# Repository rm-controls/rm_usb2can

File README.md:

# rm_usb2can

&nbsp;&nbsp;&nbsp;&nbsp;

English/[中文](https://github.com/rm-controls/rm_usb2can/blob/main/README_CN.md)

***

### Brief Introduction

&nbsp;&nbsp;&nbsp;&nbsp;The purpose of this project is to provide [Intel® NUC](https://www.intel.com/content/www/us/en/products/details/nuc.html) and other x86 device with a CAN (Controller Area Network) peripheral interface. Since NUC and most x86 device does not have simple peripheral interfaces such as SPI (Serial Peripheral Interface), it is impossible to use SPI to can chips such as MCP2515. Therefore, the project is developed based on the open source solution [candleLight](https://github.com/candle-usb/candleLight_fw/tree/master) on GitHub, and STM32F072CBT6 is used as the main control chip to realize the function of USB (Universal Serial Bus) to can. STM32F072CBT6 has USB full speed peripherals and can peripherals that can work at the same time. It is packaged as QFP48 (Quad Flat Package) and is an excellent solution.The following figure shows the physical connection between Intel NUC and usb2can.

***

### Develop Tools

+ EDA Tool: KiCAD 6.0.9
+ Compiler: gcc-arm-none-eabi 10.3.1 20210824 (release)
+ Programming Tool: STM32CubeProgrammer v2.13.0

***

### Directory Structure

+ manufacture: USB2CAN production manufacturing file.
+ program: Github open source program [candleLight](https://github.com/candle-usb/candleLight_fw/tree/master) modified source code.
+ circuit: Circuit schematic and PCB source files designed with KiCAD.
+ image: Images of README.

***

### Circuit Design

#### Key Points Of Schematic Design

&nbsp;&nbsp;&nbsp;&nbsp;USB HUB Circuit Design: since the whole vehicle needs at least two can buses to ensure the integrity of the data packet returned by the motor, we use SL2.1s as the USB HUB chip to realize the scheme of USB one driving four. In addition, we also use Schmidt trigger to realize the power on sequence to ensure that the enumeration sequence of USB devices is consistent after each power on.

&nbsp;&nbsp;&nbsp;&nbsp;USB To CAN Circuit Design: use STM32F072CBT6 to realize the function of USB to can. The CAN level conversion chip uses the TJA1050 chip, which uses a 5V power supply and greatly reduces the probability of CAN transceiver damage due to the chip's higher common mode withstand voltage. The purpose of R6 and R7 resistors in the figure is to change the boot mode of STM32, so that STM32 can switch between DFU (Device Firmware Upgrade) burning mode and flash mode by changing the short circuit mode of R6 and R7, so as to facilitate firmware burning.

#### Key Points Of PCB Layout And Wiring

1. All USB buses need to be set as differential pairs, and the wiring rules of differential signals shall be strictly followed during wiring.
2. All CAN buses need to be set as differential pairs, and the wiring rules of differential signals shall be strictly followed during wiring.
3. The bottom of crystal oscillator and resonant capacitor should be hollowed out without copper.
4. The power line width shall be greater than 0.3mm as far as possible to ensure that the power track does not collapse.

***

### Circuit Making

&nbsp;&nbsp;&nbsp;&nbsp;We provide Gerber files that can be used directly for manufacturing in the [manufacturer folder](https://github.com/rm-controls/rm_usb2can/tree/main/manufacture). This version can realize one way USB to 2 way CAN + 2 way UART, and its circuit schematic is shown in the [circuit folder](https://github.com/rm-controls/rm_usb2can/tree/main/circuit). You can submit the packaged Gerber file directly to a manufacturer (e.g., [PCB Way](https://www.pcbway.com/)) for production.

&nbsp;&nbsp;&nbsp;&nbsp;You can also find the corresponding BOM (Bill Of Material) table for the board in the [manufacturer folder](https://github.com/rm-controls/rm_usb2can/tree/main/manufacture) and solder the components to the already made PCB according to this table. After the soldering is complete, please carefully check whether there is residual solder between the pins, that will lead to a short circuit on the board, and you also have to check whether the pins have the phenomenon of false solder.

&nbsp;&nbsp;&nbsp;&nbsp;After welding, use a multimeter to check whether there is a short circuit between 5V power interface and GND, and whether there is a short circuit between 3.3V power output and GND. When the above situation does not occur, connect the board to the USB port of the computer. At this time, you should see that the power indicator on the board is on, and the computer can recognize the USB HUB chip.

**Note: do not weld the up / down resistance used to switch STM32 download mode at the same time, as it may cause a short circuit between the power supply and GND!**

***

### Firmware Programming

&nbsp;&nbsp;&nbsp;&nbsp;You can download the compiled firmware in [Release](https://github.com/rm-controls/rm_usb2can/releases) page, or follow the [candlelight documentation](https://github.com/candle-usb/candleLight_fw/tree/master#building) to compile firmware by yourself. Finally, you will get the .bin file. We use [STM32CubeProgrammer](https://www.st.com/en/development-tools/stm32cubeprog.html) to burn the firmware into STM32 through USB. The steps to download firmware are shown below:

1. Remove the pull-down resistance of BOOT0 pin of STM32 and weld the pull-up resistance.
2. Connect the board to the USB port of the computer and open STM32CubeProgrammer.
3. Click the three buttons shown in the following figure in STM32CubeProgrammer to search for available STM32 devices.

4. After successful connection, click the "Read" button to read the firmware and select the prepared firmware.

5. Click "Download" to download the firmware. After the download is successful, you can see the successful information.

6. Remove the pull-up resistance of BOOT0 pin on STM32 and weld the pull-down resistance. Power on again at this time, and the firmware will start running on STM32.

***

### Test Features On Ubuntu

1. Install dependent packages:

```bash
$ sudo apt-get update && sudo apt-get -y upgrade
$ sudo apt-get install -y can-utils net-tools
```

2. Check whether can device is detected:

```bash
$ ifconfig -a
# If a device with can name is found in the list, it means that the device can be recognized
```

3. Connect the two can ports with a **straight line** to facilitate loop back test.
4. Initialize CAN0 and CAN1 devices with a bit rate of 1Mbits:

```bash
$ sudo ip link set can0 up type can bitrate 1000000
$ sudo ip link set can1 up type can bitrate 1000000
```

5. Open a new terminal to monitor the information received by can0:

```bash
$ candump can0
```

6. Sending information using can1 in a terminal:

```bash
$ cansend can1 200#5A5A5A5A5A5A5A5A
```

If you can see the following information from can1 in the terminal monitoring can0, it indicates that the communication is successful and the module works normally.

```bash
can0 200 [8] 5A 5A 5A 5A 5A 5A 5A 5A
```

***

### License

The source code is released under a [MIT License](https://github.com/rm-controls/rm_usb2can/blob/main/LICENSE).

**Affiliation：DynamicX<br>
Maintainer：YanzhenZhu, 2208213223@qq.com**

The product has been tested under Ubuntu 18.04, 20.04 and 22.04. This is research code, expect that it changes often and any fitness for a particular purpose is disclaimed.

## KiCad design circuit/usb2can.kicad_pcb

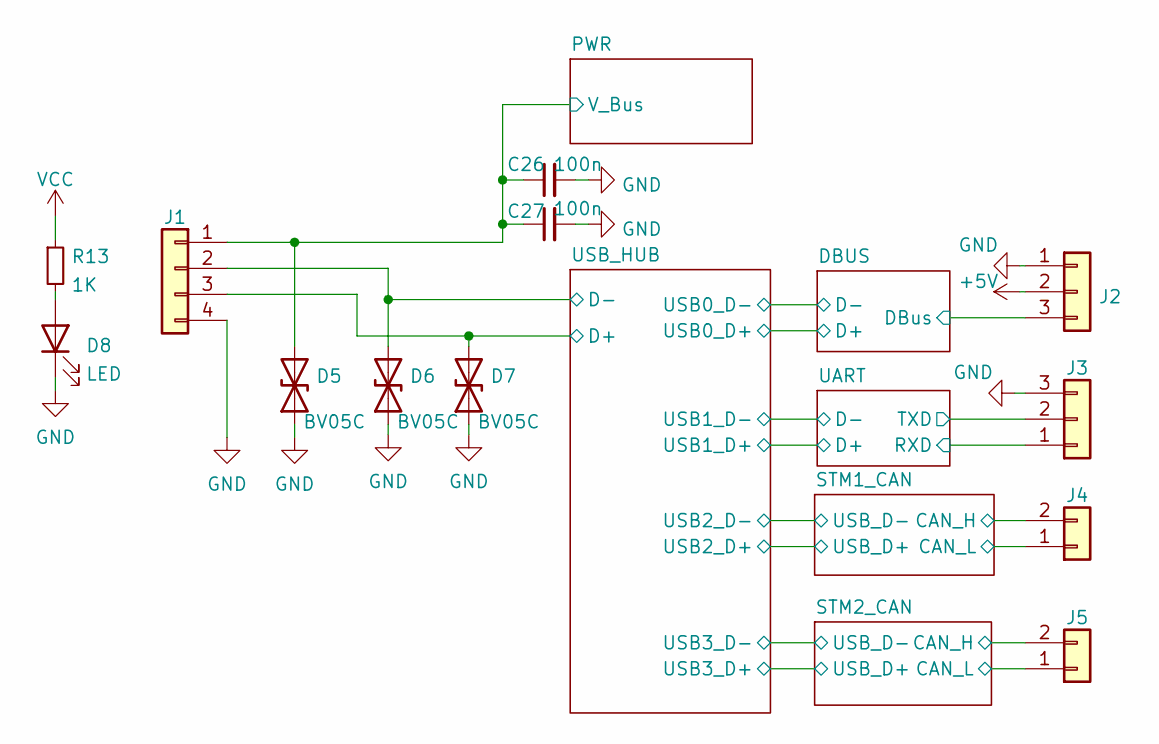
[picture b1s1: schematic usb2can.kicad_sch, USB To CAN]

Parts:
C26, C27: 100n; C_0603_1608Metric
D5, D6, D7: BV05C; D_SOD-323
D8: LED; LED_0603_1608Metric
J1: Conn_01x04; Molex_CLIK-Mate_502386-0470_1x04-1MP_P1.25mm_Horizontal
J2, J3: Conn_01x03; JST_GH_SM03B-GHS-TB_1x03-1MP_P1.25mm_Horizontal
J4, J5: Conn_01x02; JST_GH_SM02B-GHS-TB_1x02-1MP_P1.25mm_Horizontal
R13: 1K; R_0603_1608Metric

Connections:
+5V: C26.1, C27.1, D5.2 (A2), J1.1, J2.2; also elsewhere on the board
/DBUS/DBus: J2.3; also elsewhere on the board
/STM1_CAN/CAN_H: J4.2; also elsewhere on the board
/STM1_CAN/CAN_L: J4.1; also elsewhere on the board
/STM2_CAN/CAN_H: J5.2; also elsewhere on the board
/STM2_CAN/CAN_L: J5.1; also elsewhere on the board
/UART/RXD: J3.1; also elsewhere on the board
/UART/TXD: J3.2; also elsewhere on the board
/USB_HUB/D+: D7.2 (A2), J1.3; also elsewhere on the board
/USB_HUB/D-: D6.2 (A2), J1.2; also elsewhere on the board
GND: C26.2, C27.2, D5.1 (A1), D6.1 (A1), D7.1 (A1), D8.1 (K), J1.4, J2.1, J3.3; also elsewhere on the board
unnamed: D8.2 (A), R13.2
VCC: R13.1; also elsewhere on the board

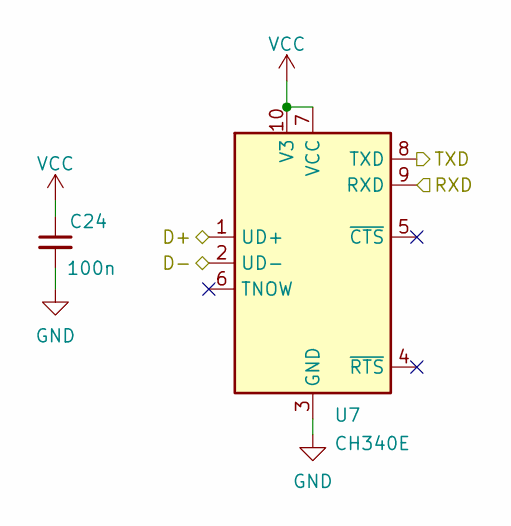
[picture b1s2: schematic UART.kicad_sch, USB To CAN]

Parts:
C24: 100n; C_0603_1608Metric
U7: CH340E; MSOP-10_3x3mm_P0.5mm

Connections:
/UART/D+: U7.1 (UD+); also elsewhere on the board
/UART/D-: U7.2 (UD-); also elsewhere on the board
/UART/RXD: U7.9 (RXD); also elsewhere on the board
/UART/TXD: U7.8 (TXD); also elsewhere on the board
GND: C24.2, U7.3 (GND); also elsewhere on the board
VCC: C24.1, U7.7 (VCC), U7.10 (V3); also elsewhere on the board

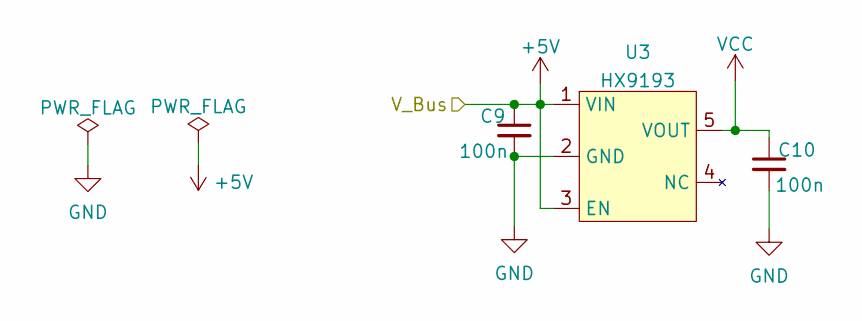
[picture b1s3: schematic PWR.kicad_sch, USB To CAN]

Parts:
C9, C10: 100n; C_0603_1608Metric
U3: HX9193; SOT-23-5_HandSoldering

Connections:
+5V: C9.1, U3.1 (VIN), U3.3 (EN); also elsewhere on the board
GND: C9.2, C10.2, U3.2 (GND); also elsewhere on the board
VCC: C10.1, U3.5 (VOUT); also elsewhere on the board

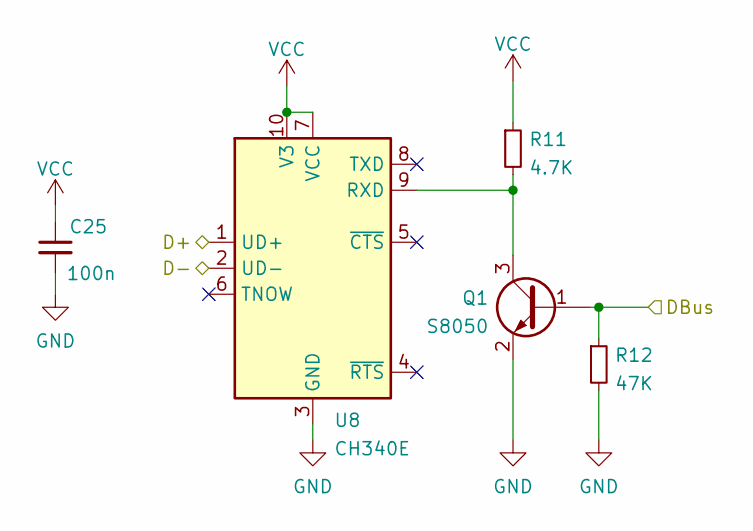
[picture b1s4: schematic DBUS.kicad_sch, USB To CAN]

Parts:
C25: 100n; C_0603_1608Metric
Q1: S8050; SOT-23
R11: 4.7K; R_0603_1608Metric
R12: 47K; R_0603_1608Metric
U8: CH340E; MSOP-10_3x3mm_P0.5mm

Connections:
/DBUS/D+: U8.1 (UD+); also elsewhere on the board
/DBUS/D-: U8.2 (UD-); also elsewhere on the board
/DBUS/DBus: Q1.1 (B), R12.1; also elsewhere on the board
GND: C25.2, Q1.2 (E), R12.2, U8.3 (GND); also elsewhere on the board
unnamed: Q1.3 (C), R11.2, U8.9 (RXD)
VCC: C25.1, R11.1, U8.7 (VCC), U8.10 (V3); also elsewhere on the board

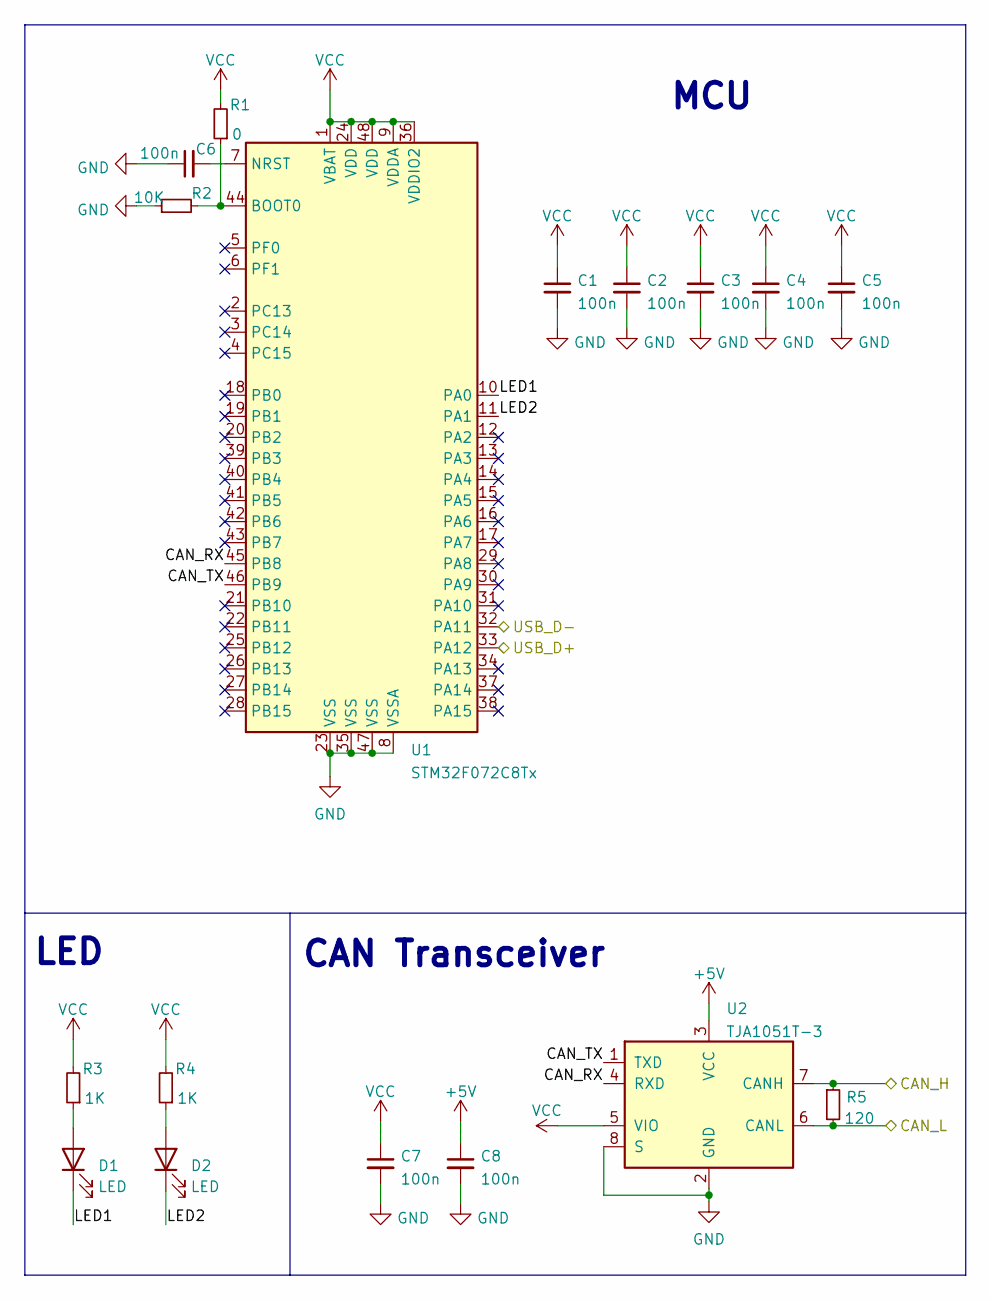
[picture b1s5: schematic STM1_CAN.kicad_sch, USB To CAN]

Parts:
C1, C2, C3, C4, C5, C6, C7, C8: 100n; C_0603_1608Metric
D1, D2: LED; LED_0603_1608Metric
R1: 0; R_0603_1608Metric
R2: 10K; R_0603_1608Metric
R3, R4: 1K; R_0603_1608Metric
R5: 120; R_0603_1608Metric
U1: STM32F072C8Tx; LQFP-48_7x7mm_P0.5mm
U2: TJA1051T-3; SOIC-8_3.9x4.9mm_P1.27mm

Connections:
+5V: C8.1, U2.3 (VCC); also elsewhere on the board
/STM1_CAN/CAN_H: R5.1, U2.7 (CANH); also elsewhere on the board
/STM1_CAN/CAN_L: R5.2, U2.6 (CANL); also elsewhere on the board
/STM1_CAN/CAN_RX: U1.45 (PB8), U2.4 (RXD)
/STM1_CAN/CAN_TX: U1.46 (PB9), U2.1 (TXD)
/STM1_CAN/LED1: D1.1 (K), U1.10 (PA0)
/STM1_CAN/LED2: D2.1 (K), U1.11 (PA1)
/STM1_CAN/USB_D+: U1.33 (PA12); also elsewhere on the board
/STM1_CAN/USB_D-: U1.32 (PA11); also elsewhere on the board
GND: C1.2, C2.2, C3.2, C4.2, C5.2, C6.1, C7.2, C8.2, R2.1, U1.8 (VSSA), U1.23 (VSS), U1.35 (VSS), U1.47 (VSS), U2.2 (GND), U2.8 (S); also elsewhere on the board
unnamed: C6.2, U1.7 (NRST)
unnamed: D1.2 (A), R3.1
unnamed: D2.2 (A), R4.1
unnamed: R1.1, R2.2, U1.44 (BOOT0)
VCC: C1.1, C2.1, C3.1, C4.1, C5.1, C7.1, R1.2, R3.2, R4.2, U1.1 (VBAT), U1.9 (VDDA), U1.24 (VDD), U1.36 (VDDIO2), U1.48 (VDD), U2.5 (VIO); also elsewhere on the board

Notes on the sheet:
CAN Transceiver
LED
MCU

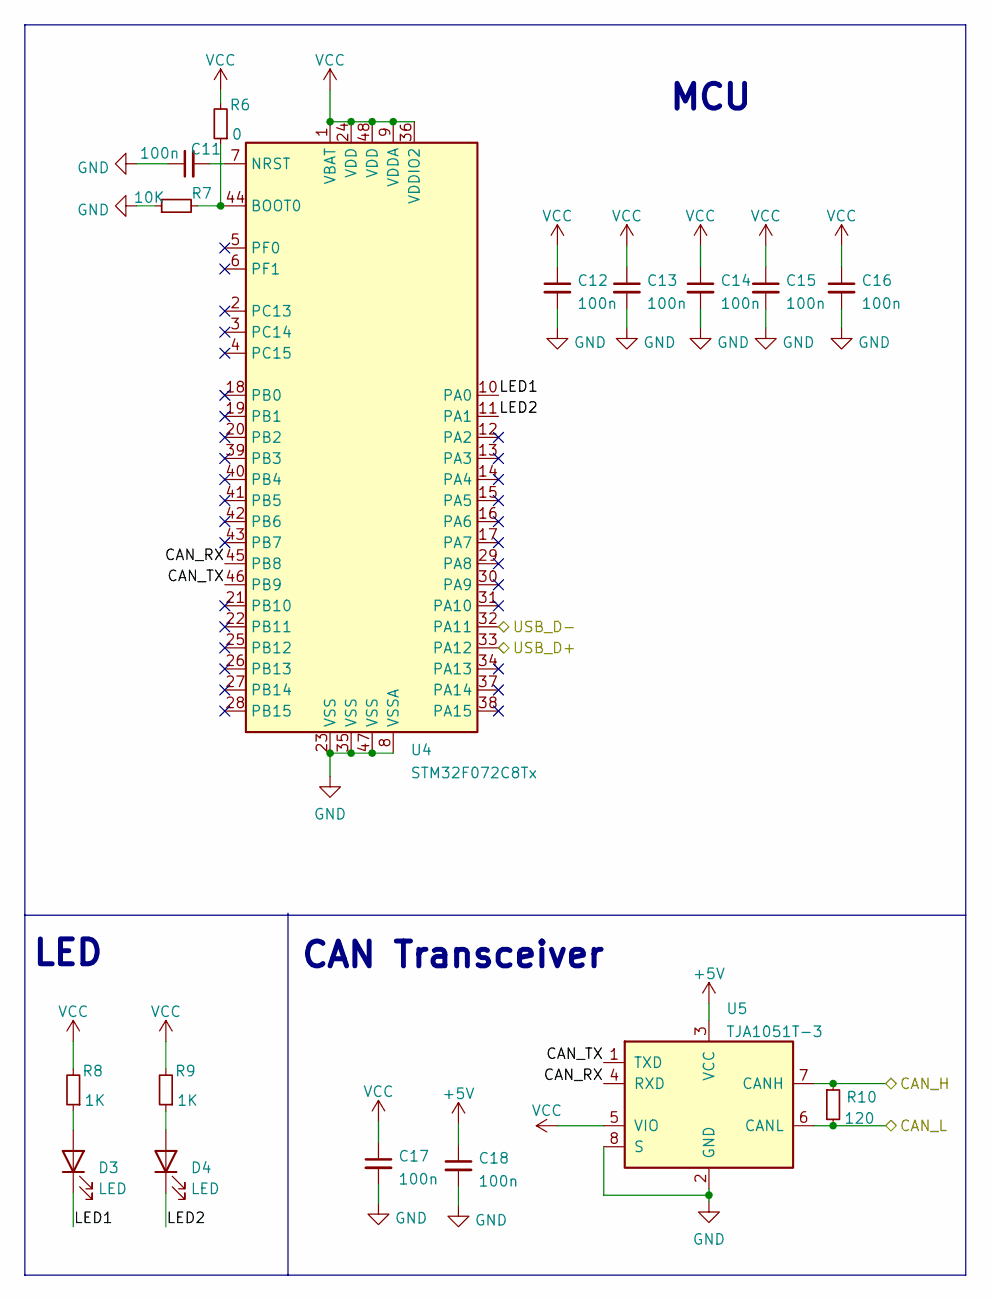
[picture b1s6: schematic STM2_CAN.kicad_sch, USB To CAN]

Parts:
C11, C12, C13, C14, C15, C16, C17, C18: 100n; C_0603_1608Metric
D3, D4: LED; LED_0603_1608Metric
R6: 0; R_0603_1608Metric
R7: 10K; R_0603_1608Metric
R8, R9: 1K; R_0603_1608Metric
R10: 120; R_0603_1608Metric
U4: STM32F072C8Tx; LQFP-48_7x7mm_P0.5mm
U5: TJA1051T-3; SOIC-8_3.9x4.9mm_P1.27mm

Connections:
+5V: C18.1, U5.3 (VCC); also elsewhere on the board
/STM2_CAN/CAN_H: R10.1, U5.7 (CANH); also elsewhere on the board
/STM2_CAN/CAN_L: R10.2, U5.6 (CANL); also elsewhere on the board
/STM2_CAN/CAN_RX: U4.45 (PB8), U5.4 (RXD)
/STM2_CAN/CAN_TX: U4.46 (PB9), U5.1 (TXD)
/STM2_CAN/LED1: D3.1 (K), U4.10 (PA0)
/STM2_CAN/LED2: D4.1 (K), U4.11 (PA1)
/STM2_CAN/USB_D+: U4.33 (PA12); also elsewhere on the board
/STM2_CAN/USB_D-: U4.32 (PA11); also elsewhere on the board
GND: C11.1, C12.2, C13.2, C14.2, C15.2, C16.2, C17.2, C18.2, R7.1, U4.8 (VSSA), U4.23 (VSS), U4.35 (VSS), U4.47 (VSS), U5.2 (GND), U5.8 (S); also elsewhere on the board
unnamed: C11.2, U4.7 (NRST)
unnamed: D3.2 (A), R8.1
unnamed: D4.2 (A), R9.1
unnamed: R6.1, R7.2, U4.44 (BOOT0)
VCC: C12.1, C13.1, C14.1, C15.1, C16.1, C17.1, R6.2, R8.2, R9.2, U4.1 (VBAT), U4.9 (VDDA), U4.24 (VDD), U4.36 (VDDIO2), U4.48 (VDD), U5.5 (VIO); also elsewhere on the board

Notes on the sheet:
LED
MCU
CAN Transceiver

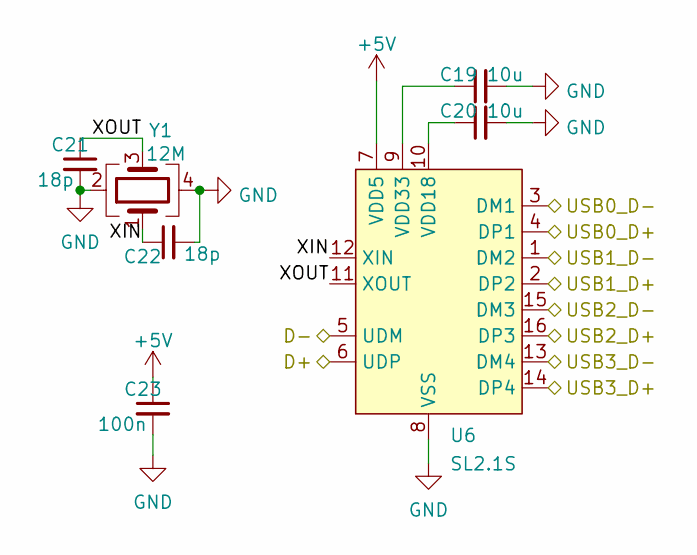
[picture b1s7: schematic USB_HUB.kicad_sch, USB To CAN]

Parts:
C19, C20: 10u; C_0603_1608Metric
C21, C22: 18p; C_0603_1608Metric
C23: 100n; C_0603_1608Metric
U6: SL2.1S; SL2.1S-SSOP-16
Y1: 12M; Crystal_SMD_3225-4Pin_3.2x2.5mm

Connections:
+5V: C23.1, U6.7 (VDD5); also elsewhere on the board
/DBUS/D+: U6.4 (DP1); also elsewhere on the board
/DBUS/D-: U6.3 (DM1); also elsewhere on the board
/STM1_CAN/USB_D+: U6.16 (DP3); also elsewhere on the board
/STM1_CAN/USB_D-: U6.15 (DM3); also elsewhere on the board
/STM2_CAN/USB_D+: U6.14 (DP4); also elsewhere on the board
/STM2_CAN/USB_D-: U6.13 (DM4); also elsewhere on the board
/UART/D+: U6.2 (DP2); also elsewhere on the board
/UART/D-: U6.1 (DM2); also elsewhere on the board
/USB_HUB/D+: U6.6 (UDP); also elsewhere on the board
/USB_HUB/D-: U6.5 (UDM); also elsewhere on the board
/USB_HUB/XIN: C22.1, U6.12 (XIN), Y1.1
/USB_HUB/XOUT: C21.1, U6.11 (XOUT), Y1.3
GND: C19.2, C20.2, C21.2, C22.2, C23.2, U6.8 (VSS), Y1.2, Y1.4; also elsewhere on the board
unnamed: C19.1, U6.9 (VDD33)
unnamed: C20.1, U6.10 (VDD18)

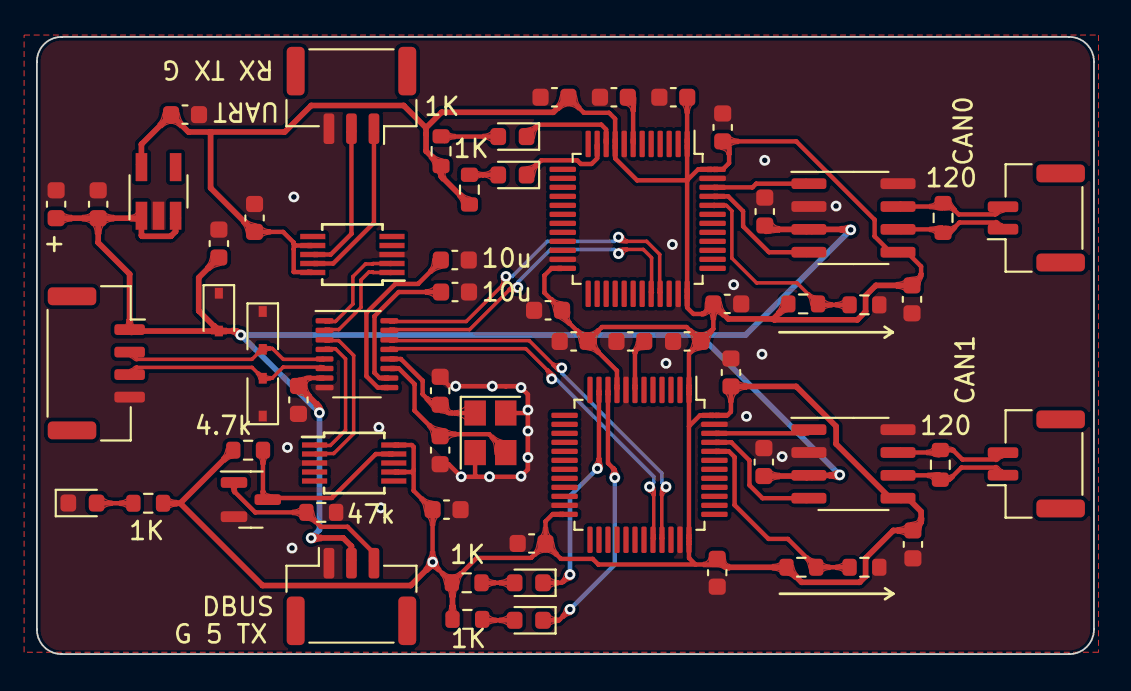
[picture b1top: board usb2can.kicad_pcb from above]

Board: 2 copper layers, 58.7 x 34.3 mm, 63 parts (0 on the bottom side), 42 nets.

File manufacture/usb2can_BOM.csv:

"ID";"指示符";"软件包";"数量";"名称";"供应商和参考";
1;"D3,D2,D1,D4,D8";"LED_0603_1608Metric";5;"LED";;;
2;"C9,C6,C26,C25,C5,C27,C16,C10,C7,C23,C17,C24,C12,C18,C2,C14,C3,C11,C13,C8,C1,C15,C4";"C_0603_1608Metric";23;"100n";;;
3;"R8,R4,R9,R3,R13";"R_0603_1608Metric";5;"1K";;;
4;"U5,U2";"SOIC-8_3.9x4.9mm_P1.27mm";2;"TJA1051T-3";;;
5;"U4,U1";"LQFP-48_7x7mm_P0.5mm";2;"STM32F072C8Tx";;;
6;"U6";"SL2.1S-SSOP-16";1;"SL2.1S";;;
7;"J1";"Molex_CLIK-Mate_502386-0470_1x04-1MP_P1.25mm_Horizontal";1;"Conn_01x04";;;
8;"C21,C22";"C_0603_1608Metric";2;"18p";;;
9;"Q1";"SOT-23";1;"S8050";;;
10;"J4,J5";"JST_GH_SM02B-GHS-TB_1x02-1MP_P1.25mm_Horizontal";2;"Conn_01x02";;;
11;"U3";"SOT-23-5_HandSoldering";1;"HX9193";;;
12;"D7,D5,D6";"D_SOD-323";3;"BV05C";;;
13;"R6,R1";"R_0603_1608Metric";2;"0";;;
14;"R11";"R_0603_1608Metric";1;"4.7K";;;
15;"R5,R10";"R_0603_1608Metric";2;"120";;;
16;"R2,R7";"R_0603_1608Metric";2;"10K";;;
17;"U7,U8";"MSOP-10_3x3mm_P0.5mm";2;"CH340E";;;
18;"R12";"R_0603_1608Metric";1;"47K";;;
19;"J3,J2";"JST_GH_SM03B-GHS-TB_1x03-1MP_P1.25mm_Horizontal";2;"Conn_01x03";;;
20;"C19,C20";"C_0603_1608Metric";2;"10u";;;
21;"Y1";"Crystal_SMD_3225-4Pin_3.2x2.5mm";1;"12M";;;

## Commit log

2021-08-10 Add project files
2021-08-10 add submodule
2021-08-10 add brief introduction in readme
2021-08-10 Add develop tools in readme.md and image using in readme.
2021-08-10 add circuit design in readme
2021-08-10 Add key points of circuit design in Readme
2021-08-10 The chapter of circuit making is added in readme. The directory structure has been modified and new files are ready to be added.
2021-08-10 Added a section on firmware burning in readme
2021-08-10 Supplement the chapter 'testing functions on Ubuntu' in readme
2021-08-10 Supplement the chapter 'License' in readme
2021-08-10 Add newline symbol
2021-08-10 rearrange files
2021-08-10 Supplement the chapter 'Directory Structure' in readme
2021-08-11 Add gerber files and bom
2021-08-11 modify readme
2021-08-12 add drill files
2021-08-23 modify readme description
2021-08-29 Add the physical diagram of the connection between Intel NUC and usb2can
2021-10-04 Modify readme to mark error prone areas.
2022-05-30 Add program source code for usb2can.
2022-08-12 Update firmware link in README
2023-05-04 Update candlelight program to version 2
2023-05-04 Update newest usb2can circuit
2023-05-10 Update README and LICENSE files
2023-05-10 Add Watchdog function. Add file stm32f0xx_hal_iwdg.h,stm32f0xxhal_iwdg.c, iwdg.h, iwdg.c. Charge files stm32f0xx_hal_conf.h and stm32f0xx_hal_conf.h to config watchdog. The time of watchdog to refres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
2023-05-10 Repair manufacture factor in README
2023-05-10 Add iwdg and update library
2023-05-12 Fix iwdg bugs
2023-06-15 Modify manufacture
2023-08-08 Remove iwdg initialize code
2023-08-08 Update the code to be compatible with gcc12

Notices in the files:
README.md:
License: MIT
